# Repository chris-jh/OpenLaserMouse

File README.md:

# Open Laser Mouse
 Quadrature Optical Mouse Replacement Using an Arduino for the Amiga Tank Mouse

Version 1.4.1
Copyright 2020 Chrissy

* Updated 3D Lens Cover

Version 1.4
Copyright 2020 Chrissy

* Added Atari ST SMD Version
  * Not Tested
  * Arduino is flipped 180° for ST version
  * Use same Amiga Pin definition in Arduino source if using original ST DE9 Connector.
* Fixed Wrong Fillplane selected. Corrected it back to GND.

Version 1.3
Copyright 2020 Chrissy

* ADNS9800 interface based on code from https://github.com/mrjohnk/ADNS-9800
* QUADRATURE interface based on blog from http://danceswithferrets.org/geekblog/?p=742

Two versions of the PCB, a SMD version (v1.1 Tested, not v1.3 yet) and a THT version which is currently untested.

Requires an Arduino Nano and a ADNS9800 Laser, which you can get still get from Aliexpress. Make sure to also get the Lens.

[**SMD Interactive BOM**][IBOMSMD]

[**THT Interactive BOM**][IBOMTHT]

Gerbers have been created from the recommendations at JLCPCB.

(https://support.jlcpcb.com/article/102-kicad-515---generating-gerber-and-drill-files)

You may need to re-generate for your chosen PCB Manufacturer

get the 1.2mm PCB Thickness or get smaller height tact switches if you use 1.6mm thickness. It is a tight tolerance between the tact switch mouse buttons and the posts on the mouse buttons.

---

## 3D Printable Lens Cover

3D Printable Lens Cover still requires testing, Sketchup model file is included to modify for tolerances of your printer.
<br>Only for Amiga SMD Version at the moment

***Print Settings***

* Layer Height : 1.5mm
* Print Speed : 25 mm/s
* Initial Layer Speed: 15mm
* Support: Yes
* Infill: 20%
* Line Width: 0.4mm
* Print Thin Walls: Yes
* Filter Out Tiny Gaps: Yes

3D printed on a Ender 3 using Cura

A fully printable Amiga Tank Mouse is available here

https://www.myminifactory.com/object/3d-print-amiga-tank-mouse-all-parts-are-ultra-detailed-100-size-104702

Although looks tough to print :)

---

## !!!!! WARNING !!!!!
Don't Plug in the USB to the Arduino while connected to the Amiga/Computer, as this will join the 5V together and may damage something.

This is still a work in progress, use at your own risk. I accept no responsibility if this damages any of your equipment.

[IBOMSMD]: http://htmlpreview.github.io/?https://raw.githubusercontent.com/chris-jh/OpenLaserMouse/master/PCB/SMD/bom/ibom.html
[IBOMTHT]: http://htmlpreview.github.io/?https://raw.githubusercontent.com/chris-jh/OpenLaserMouse/master/PCB/THT/bom/ibom.html

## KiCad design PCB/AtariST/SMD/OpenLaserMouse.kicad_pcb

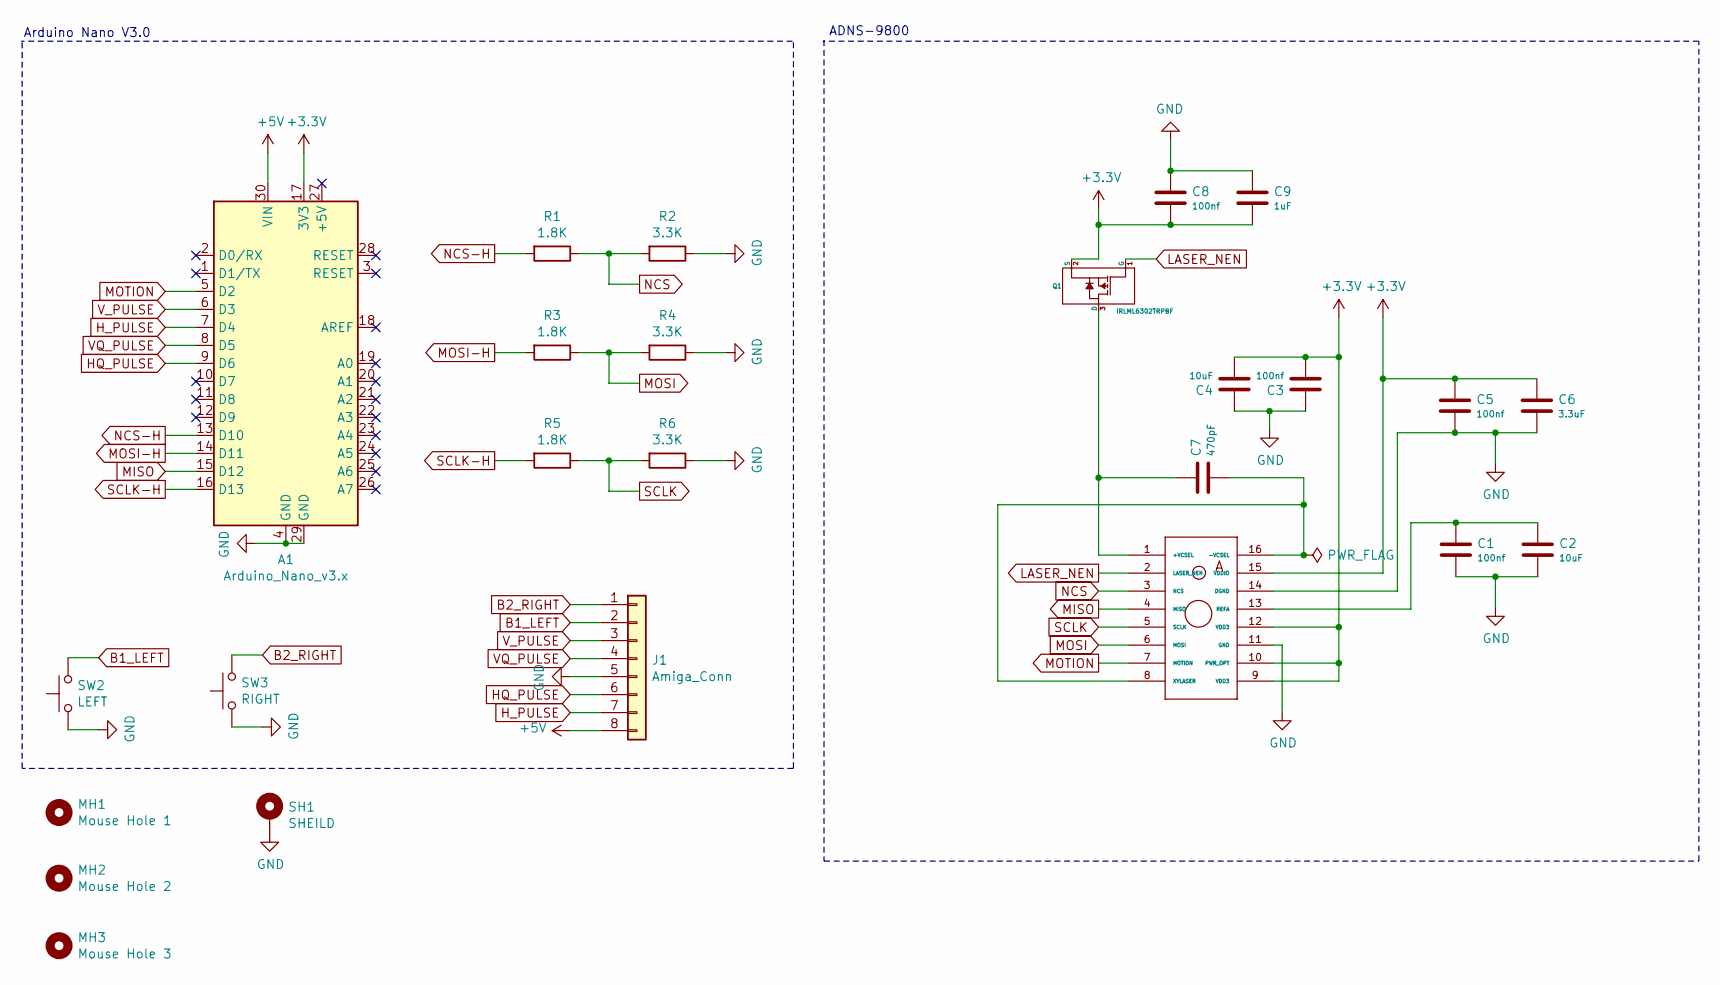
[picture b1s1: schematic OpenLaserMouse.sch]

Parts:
A1: Arduino_Nano_v3.x; Arduino_Nano
C1, C3, C5, C8: 100nf; C_0805_2012Metric
C2, C4: 10uF; C_0805_2012Metric
C6: 3.3uF; C_0805_2012Metric
C7: 470pF; C_0805_2012Metric
C9: 1uF; C_0805_2012Metric
J1: Amiga_Conn; PinHeader_1x08_P2.54mm_Vertical
M1: ADNS-9800
MH1: Mouse Hole 1; MountingHole_5.3mm_M5
MH2: Mouse Hole 2; MountingHole_5.3mm_M5
MH3: Mouse Hole 3; MountingHole_5.3mm_M5
Q1: IRLML6302TRPBF; SOT-23
R1, R3, R5: 1.8K; R_0805_2012Metric
R2, R4, R6: 3.3K; R_0805_2012Metric
SH1: SHEILD; Pin_D1.3mm_L11.0mm_LooseFit
SW2: LEFT; SW_PUSH_6mm
SW3: RIGHT; SW_PUSH_6mm

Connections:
+3V3: A1.17 (3V3), C3.2, C4.2, C5.1, C6.1, C8.2, C9.2, M1.9 (VDD3), M1.10 (PWR_OPT), M1.12 (VDD3), M1.15 (VDDIO), Q1.2 (S)
+5V: A1.30 (VIN), J1.8
B1_LEFT: J1.2, SW2.2
B2_RIGHT: J1.1, SW3.2
GND: A1.4 (GND), A1.29 (GND), C1.2, C2.2, C3.1, C4.1, C5.2, C6.2, C8.1, C9.1, J1.5, M1.11 (GND), M1.14 (DGND), R2.1, R4.1, R6.1, SH1.1, SW2.1, SW3.1
HQ_PULSE: A1.9 (D6), J1.6
H_PULSE: A1.7 (D4), J1.7
LASER_NEN: M1.2 (LASER_NEN), Q1.1 (G)
MISO: A1.15 (D12), M1.4 (MISO)
MOSI: M1.6 (MOSI), R3.1, R4.2
MOSI-H: A1.14 (D11), R3.2
MOTION: A1.5 (D2), M1.7 (MOTION)
NCS: M1.3 (NCS), R1.1, R2.2
NCS-H: A1.13 (D10), R1.2
unnamed: C1.1, C2.1, M1.13 (REFA)
unnamed: C7.1, M1.1 (+VCSEL), Q1.3 (D)
unnamed: C7.2, M1.8 (XYLASER), M1.16 (-VCSEL)
SCLK: M1.5 (SCLK), R5.1, R6.2
SCLK-H: A1.16 (D13), R5.2
VQ_PULSE: A1.8 (D5), J1.4
V_PULSE: A1.6 (D3), J1.3

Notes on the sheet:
ADNS-9800
Arduino Nano V3.0

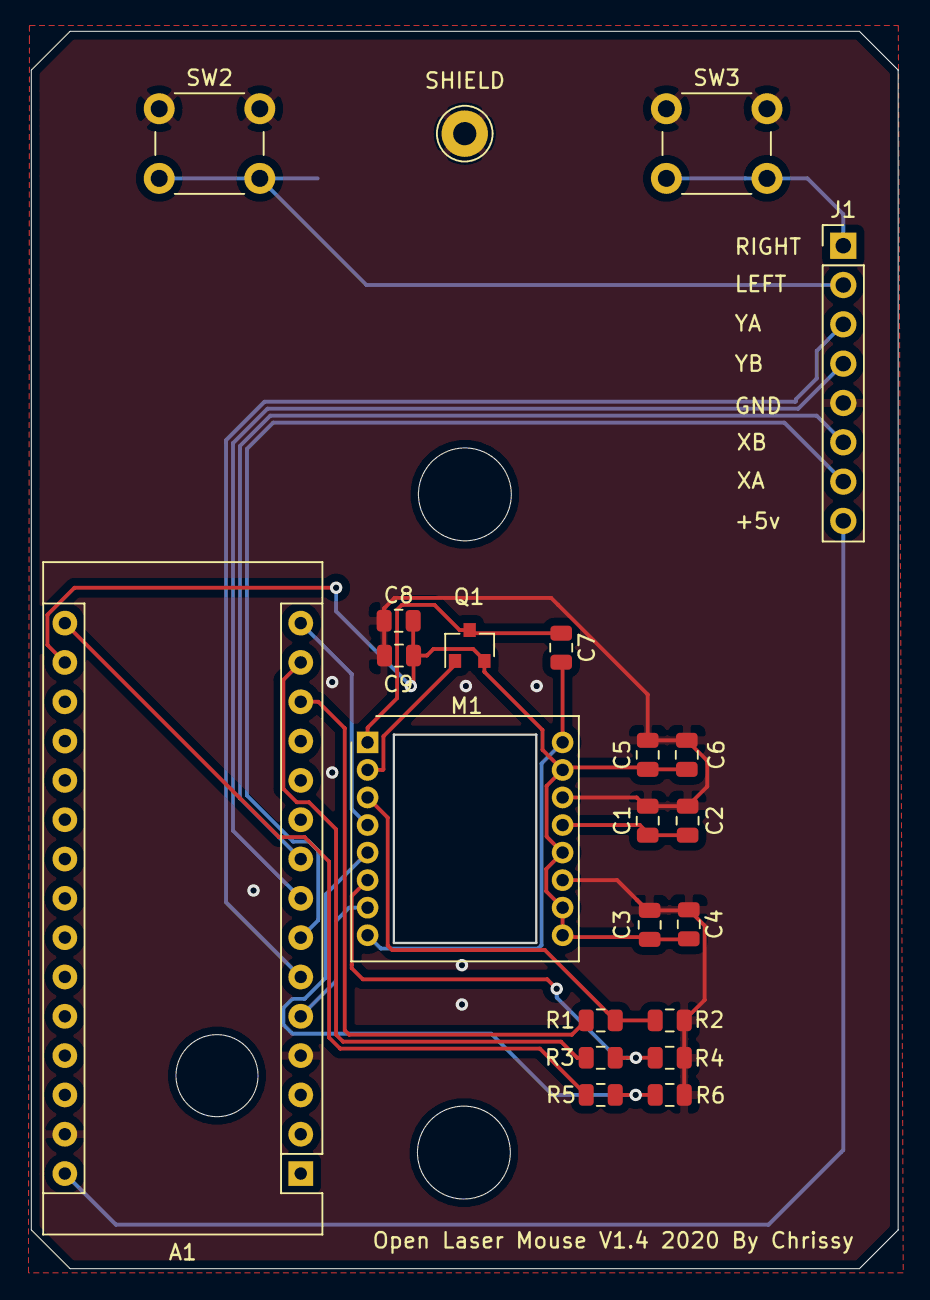
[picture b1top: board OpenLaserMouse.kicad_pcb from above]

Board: 2 copper layers, 55.9 x 79.8 mm, 25 parts (0 on the bottom side), 21 nets.

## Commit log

2020-09-06 Version fix
    Updated so all version numbers on PCB's and Code are the same
2020-09-12 Added BOM
    Added Interactive BOM
2020-09-12 Added THT BOM
    Added BOM
2020-10-14 Adjustments and Photos
    Adjusted Mouting Holes on the PCB's
    Added Photos of V1.1
    Tidy up
2020-10-15 Tidying
    Resize Images
    Added image to readme
2020-10-15 Added Gerbers
    Added Gerbers
    More Readme Tidy up
2020-11-05 Added ST Mouse PCB
    Added ST Mouse PCB
    Fixed Wrong Fillplane on Amiga PCB
2020-11-07 Update to 3D Print Lens Cover
    Update to 3D Print Lens Cover
